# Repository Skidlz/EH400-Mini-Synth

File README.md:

# EH400-Mini-Synth
A recreation of the EH400 Mini-Synthesizer from Electro Harmonix.
Includes Eagle CAD files, and gerbers
 
 #### PCB Renders ####

 #### Schematic ####

 #### Board ####

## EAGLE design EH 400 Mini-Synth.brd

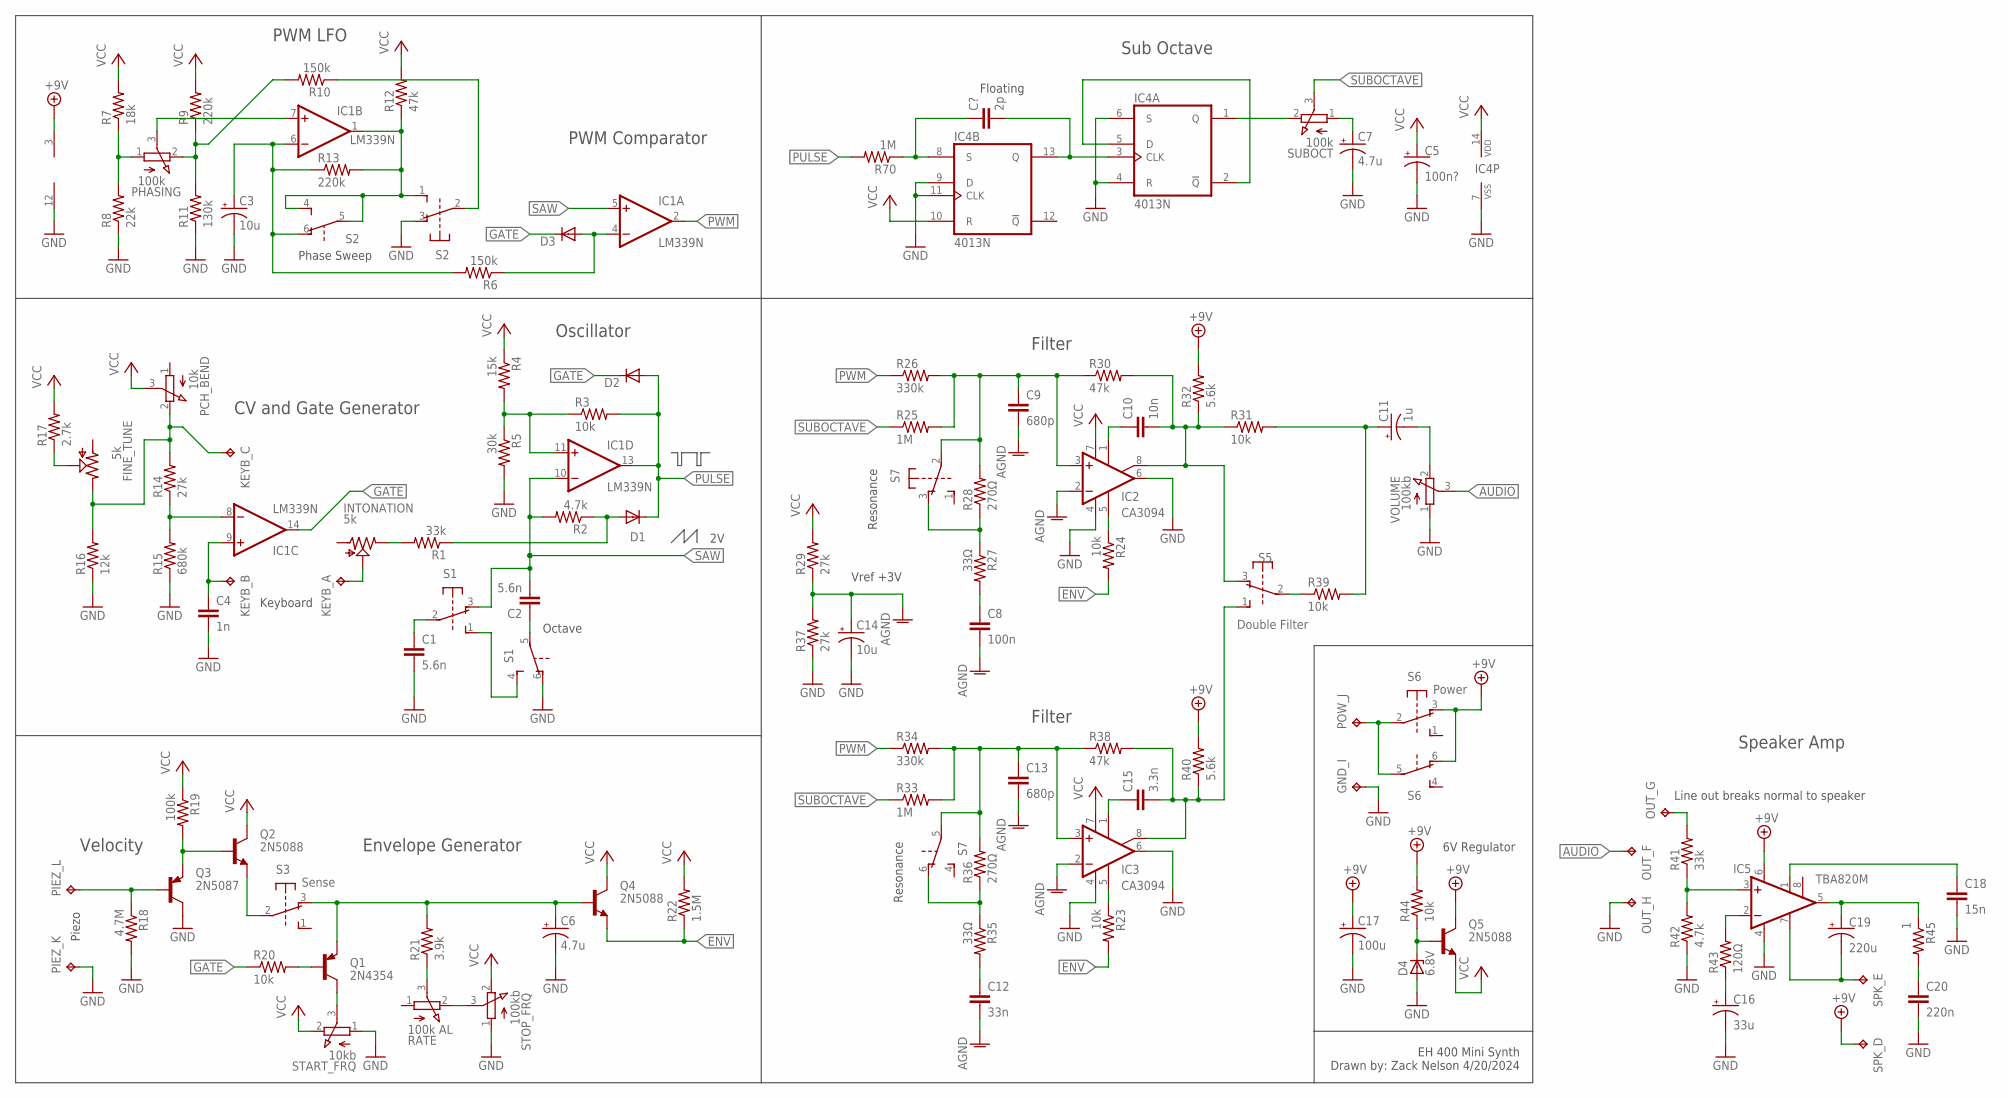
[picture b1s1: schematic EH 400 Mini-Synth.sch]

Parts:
C1, C2: 5.6n; C050-024X044
C3, C14: 10u; E3,5-8
C4: 1n; C050-024X044
C5: 100n?; E3,5-8
C6: 4.7u; E3,5-8
C7: 4.7u; E5-4
C8: 100n; C050-024X044
C9, C13: 680p; C050-024X044
C10: 10n; C050-025X075
C11: 1u; E5-4
C12: 33n; C050-024X044
C15: 3.3n; C050-024X044
C16: 33u; E3,5-8
C17: 100u; TT5D9
C18: 15n; C050-024X044
C19: 220u; TT5D9
C20: 220n; C050-024X044
C?: 2p; C075-032X103
D1, D2, D3: DIODE-DO07; DO07
D4: 6.8V; ZDIO-7.5
FINE_TUNE: 5k; ECP10S
GND_I: TPB1,27; B1,27
IC1: LM339N; DIL14
IC2, IC3: CA3094; DIL08
IC4: 4013N; DIL14
IC5: TBA820M; DIL08
INTONATION: 5k; ECP10S
KEYB_A: TPB1,27; B1,27
KEYB_B: TPB1,27; B1,27
KEYB_C: TPB1,27; B1,27
OUT_F: TPB1,27; B1,27
OUT_G: TPB1,27; B1,27
OUT_H: TPB1,27; B1,27
PCH_BEND: 10k; FADER-EHX
PHASING: 100k; FADER-EHX
PIEZ_K: TPB1,27; B1,27
PIEZ_L: TPB1,27; B1,27
POW_J: TPB1,27; B1,27
Q1: 2N4354; TO92-EBC
Q2, Q4, Q5: 2N5088; TO92-EBC
Q3: 2N5087; TO92-EBC
R1, R41: 33k; 0207/12
R2, R42: 4.7k; 0207/12
R3, R20, R23, R24, R31, R39, R44: 10k; 0207/12
R4: 15k; 0207/12
R5: 30k; 0207/12
R6, R10: 150k; 0207/12
R7: 18k; 0207/12
R8: 22k; 0207/12
R9, R13: 220k; 0207/12
R11: 130k; 0207/12
R12, R30, R38: 47k; 0207/12
R14, R29, R37: 27k; 0207/12
R15: 680k; 0207/12
R16: 12k; 0207/12
R17: 2.7k; 0207/12
R18: 4.7M; 0207/12
R19: 100k; 0207/12
R21: 3.9k; 0207/12
R22: 1.5M; 0207/12
R25, R33, R70: 1M; 0207/12
R26, R34: 330k; 0207/12
R27, R35: 33Ω; 0207/12
R28, R36: 270Ω; 0207/12
R32, R40: 5.6k; 0207/12
R43: 120Ω; 0207/12
R45: 1; 0207/12
RATE: 100k AL; FADER-EHX
S1: Octave; SLIDE
S2: Phase; SLIDE
S3: Sense; SLIDE
S5: Double Filter; SLIDE
S6: Power; SLIDE
S7: 9077-2S; SLIDE
SPK_D: TPB1,27; B1,27
SPK_E: TPB1,27; B1,27
START_FRQ: 10kb; FADER-EHX
STOP_FRQ: 100kb; FADER-EHX
SUBOCT: 100k; FADER-EHX
VOLUME: 100kb; FADER-EHX

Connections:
+9V: C17.+, IC1.3 (V+), IC5.6 (VS), Q5.C, R32.2, R40.2, R44.2, S6.3 (O), S6.6 (O), SPK_D.TP
AGND: C8.2, C9.2, C12.2, C13.2, C14.+, IC2.2 (-IN), IC3.2 (-IN), R29.1, R37.2
AUDIO: OUT_F.TP, VOLUME.3 (S)
C: FINE_TUNE.E, KEYB_C.TP, PCH_BEND.2 (E), R14.2, R16.2
ENV: Q4.E, R22.1, R23.2, R24.2
GATE: D2.C, D3.C, IC1.14 (OUT), R20.1
GND: C1.2, C3.-, C4.2, C5.-, C6.-, C7.-, C14.-, C16.-, C17.-, C18.2, C20.2, D4.A, GND_I.TP, IC1.12 (GND), IC2.4 (V-), IC2.6 (OUT), IC3.4 (V-), IC3.6 (OUT), IC4.4 (R), IC4.6 (S), IC4.7 (VSS), IC4.9 (D), IC4.11 (CLK), IC5.4 (GND), OUT_H.TP, PIEZ_K.TP, Q3.C, R5.2, R8.1, R11.1, R15.1, R16.1, R18.2, R37.1, R42.1, S1.6 (O), S2.3 (O), START_FRQ.1 (A), STOP_FRQ.1 (A), VOLUME.1 (A)
LFO_TRI: C3.+, IC1.6 (-IN), R6.2, R13.1, S2.6 (O)
unnamed: C?.1, IC4.8 (S), R70.1
unnamed: D1.A, R1.1, R2.1
unnamed: INTONATION.E, R1.2
unnamed: IC1.11 (+IN), R3.1, R4.2, R5.1
unnamed: C?.2, IC4.3 (CLK), IC4.13 (Q)
unnamed: IC1.1 (OUT), R12.1, R13.2, S2.1 (S), S2.4 (S), S2.5
unnamed: D3.A, IC1.4 (-IN), R6.1
unnamed: IC4.2 (!Q), IC4.5 (D)
unnamed: PIEZ_L.TP, Q3.B, R18.1
unnamed: S1.1 (S), S1.4 (S)
unnamed: C1.1, S1.2
unnamed: C2.1, S1.5
unnamed: PHASING.1 (A), R7.1, R8.2
unnamed: PHASING.2 (E), R9.1, R10.2, R11.2
unnamed: IC1.7 (+IN), PHASING.3 (S)
unnamed: R10.1, S2.2
unnamed: Q2.B, Q3.E, R19.2
unnamed: C4.1, IC1.9 (+IN), KEYB_B.TP
unnamed: INTONATION.S, KEYB_A.TP
unnamed: IC1.8 (-IN), R14.1, R15.2
unnamed: Q2.E, S3.2
unnamed: FINE_TUNE.S, R17.1
unnamed: RATE.2 (E), STOP_FRQ.3 (S)
unnamed: C19.+, IC5.5 (OUT), R45.1
unnamed: C6.+, Q1.E, Q4.B, R21.2, S3.3 (O)
unnamed: Q1.B, R20.2
unnamed: R21.1, RATE.3 (S)
unnamed: Q1.C, START_FRQ.3 (S)
unnamed: C18.1, IC5.1 (GAIN)
unnamed: C7.+, SUBOCT.1 (A)
unnamed: R39.1, S5.2
unnamed: IC2.5 (OPT), R24.1
unnamed: C9.1, IC2.3 (+IN), R25.2, R26.2, R28.2, R30.1, S7.2
unnamed: IC4.1 (Q), SUBOCT.2 (E)
unnamed: C8.1, R27.2
unnamed: C10.2, IC2.8 (ON2), R30.2, R31.1, R32.1, S5.3 (O)
unnamed: R27.1, R28.1, S7.3 (O)
unnamed: IC3.5 (OPT), R23.1
unnamed: C10.1, IC2.1 (ON1)
unnamed: C12.1, R35.2
unnamed: R35.1, R36.1, S7.6 (O)
unnamed: C15.1, IC3.1 (ON1)
unnamed: C15.2, IC3.8 (ON2), R38.2, R40.1, S5.1 (S)
unnamed: C13.1, IC3.3 (+IN), R33.2, R34.2, R36.2, R38.1, S7.5
unnamed: C11.+, R31.2, R39.2
unnamed: C11.-, VOLUME.2 (E)
unnamed: C20.1, R45.2
unnamed: C19.-, IC5.7 (BYPASS), SPK_E.TP
unnamed: D4.C, Q5.B, R44.1
unnamed: IC5.2 (-IN), R43.2
unnamed: C16.+, R43.1
unnamed: OUT_G.TP, R41.2
unnamed: IC5.3 (+IN), R41.1, R42.2
unnamed: POW_J.TP, S6.2, S6.5
PULSE: D1.C, D2.A, IC1.13 (OUT), R3.2, R70.2
PWM: IC1.2 (OUT), R26.1, R34.1
SAW: C2.2, IC1.5 (+IN), IC1.10 (-IN), R2.2, S1.3 (O)
SUBOCTAVE: R25.1, R33.1, SUBOCT.3 (S)
VCC: C5.+, IC2.7 (V+), IC3.7 (V+), IC4.10 (R), IC4.14 (VDD), PCH_BEND.3 (S), Q2.C, Q4.C, Q5.E, R4.1, R7.2, R9.2, R12.2, R17.2, R19.1, R22.2, R29.2, START_FRQ.2 (E), STOP_FRQ.2 (E)

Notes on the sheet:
Phase Sweep
Octave
Oscillator
CV and Gate Generator
PWM LFO
PWM Comparator
Envelope Generator
6V Regulator
EH 400 Mini Synth Drawn by: Zack Nelson 4/20/2024
Vref +3V
Velocity
Filter
Resonance
Sub Octave
Floating
Line out breaks normal to speaker
Piezo
Keyboard
Speaker Amp

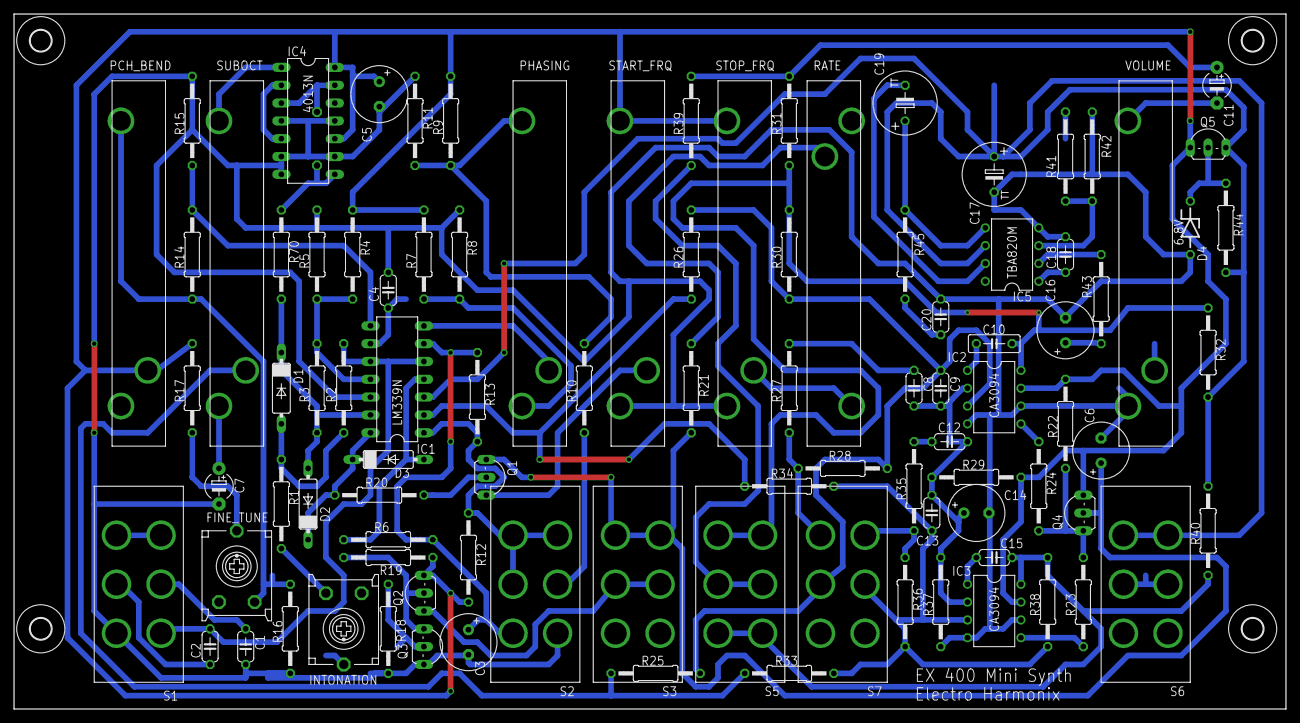
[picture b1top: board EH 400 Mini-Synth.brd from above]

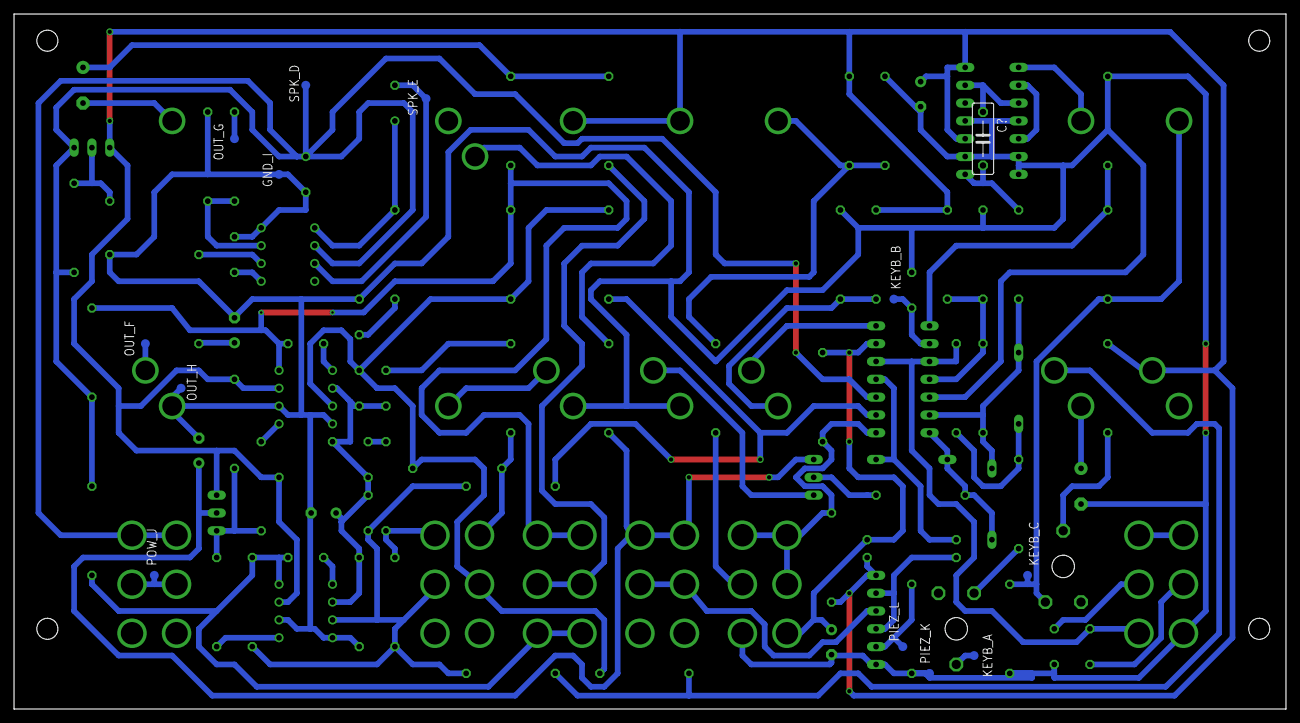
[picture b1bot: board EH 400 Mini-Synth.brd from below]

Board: 2 copper layers, 181.3 x 99.0 mm, 112 parts (13 on the bottom side), 67 nets.

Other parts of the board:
U$1, U$2, U$3, U$4: 3,0

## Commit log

2025-03-30 Init
2025-07-15 Adding scans
